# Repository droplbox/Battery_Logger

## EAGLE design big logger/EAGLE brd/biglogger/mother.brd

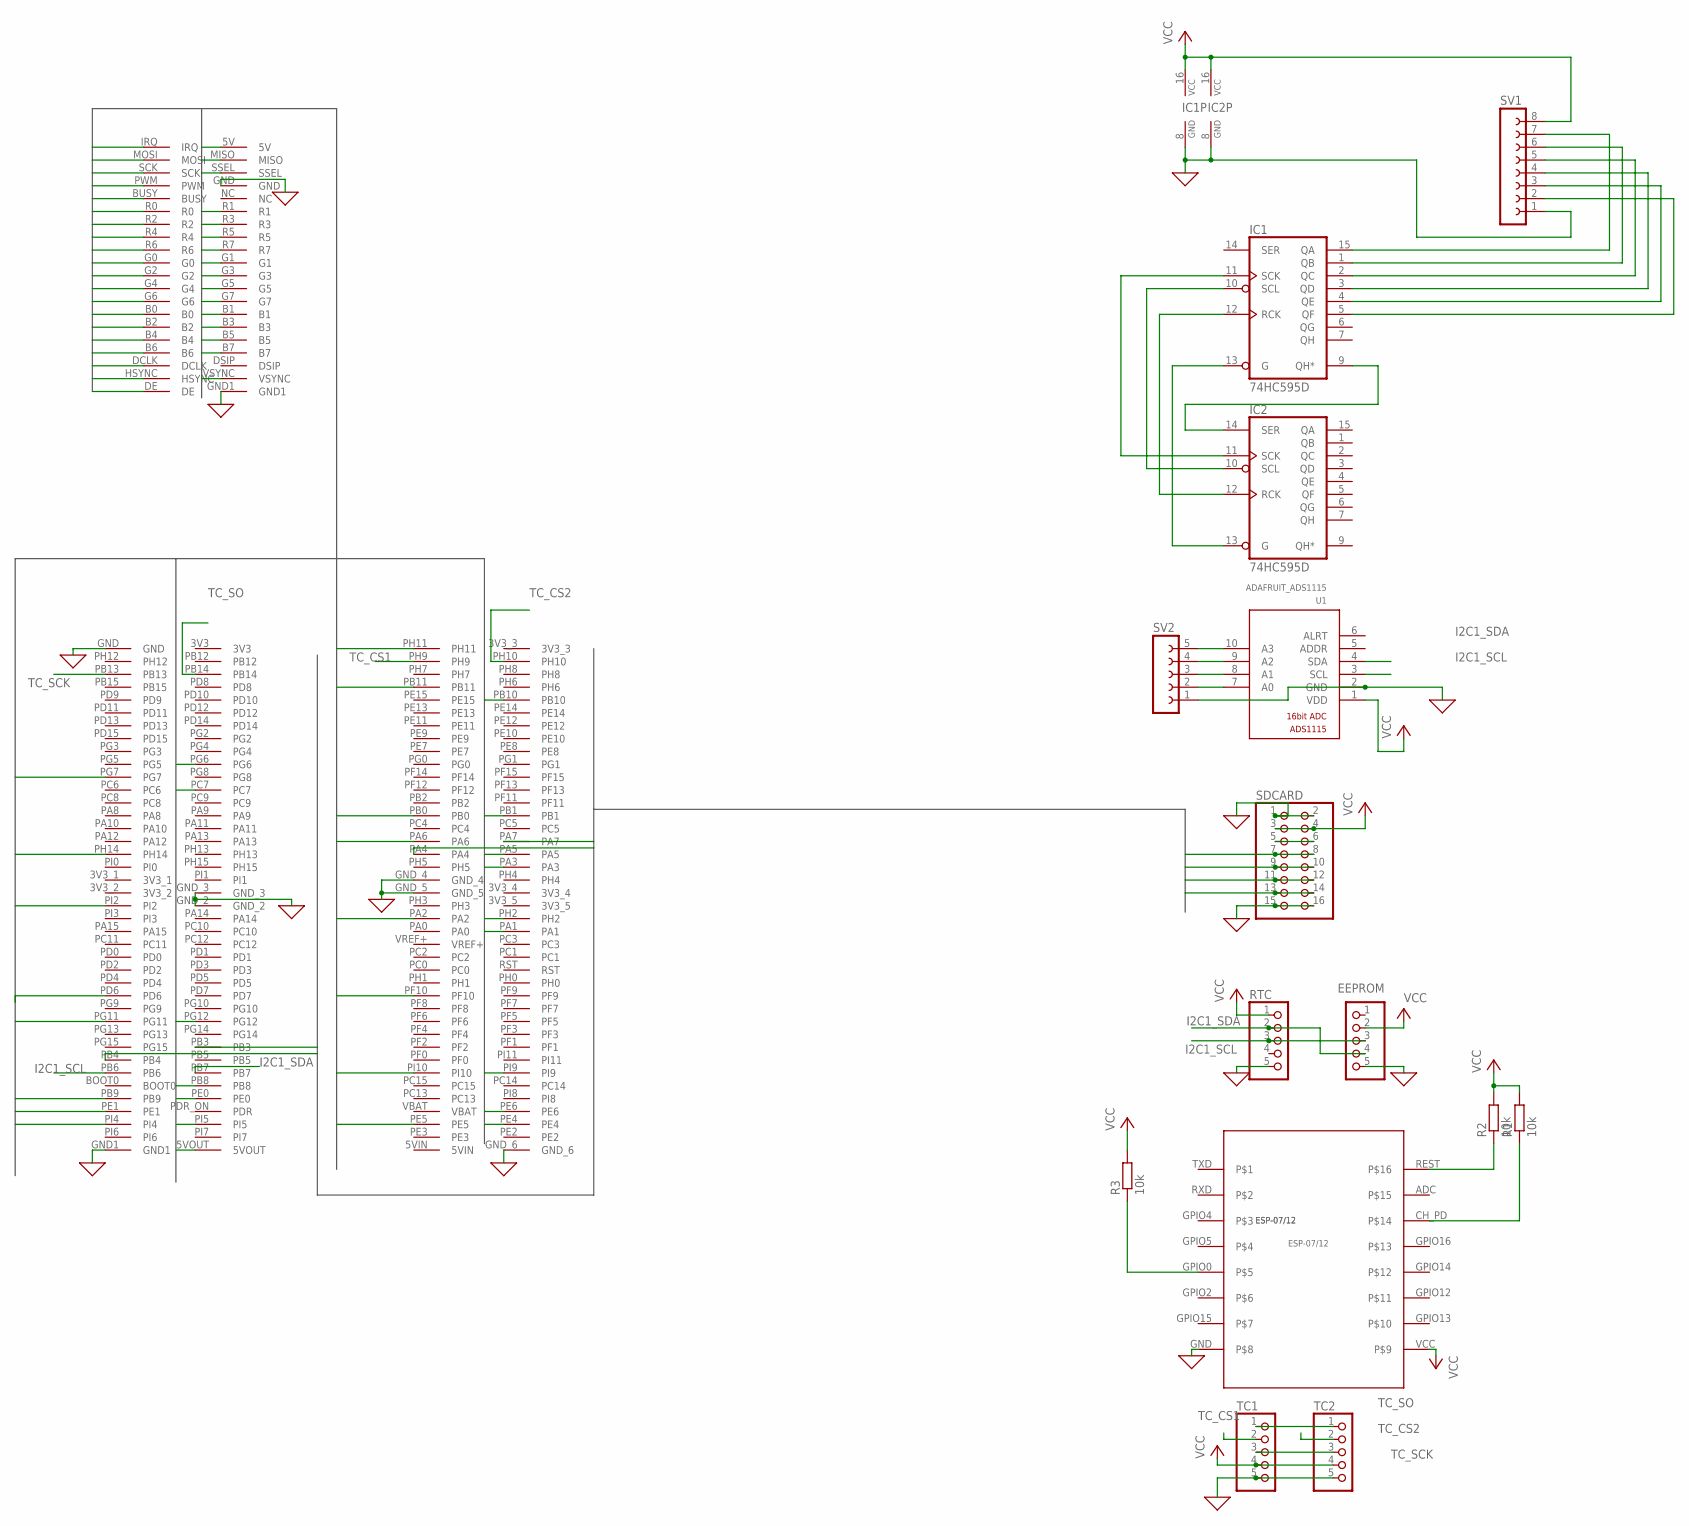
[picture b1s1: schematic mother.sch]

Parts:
EEPROM: PINHD-1X5; 1X05
IC1, IC2: 74HC595D; SO16
R1, R2, R3: 10k; R1206
RTC: PINHD-1X5; 1X05
SDCARD: PINHD-2X8; 2X08
SV1: FE08-1; FE08
SV2: FE05-1
TC1, TC2: PINHD-1X5; 1X05
U1: ADAFRUIT_ADS1115; ADAFRUIT_ADS1115_16BIT_I2C_ADC
U$1: LCDTFT; 4.3LCDTFT
U$2: HEADER2X40_2MM; HEADER
U$3: ESP-07/12

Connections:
0: EEPROM.5, IC1.8 (GND), IC2.8 (GND), RTC.5, SDCARD.1, SDCARD.2, SDCARD.15, SDCARD.16, SV1.1, SV2.1, TC1.5, TC2.5, U1.2 (GND), U$1.GND, U$1.GND1, U$2.GND, U$2.GND1, U$2.GND_2, U$2.GND_3, U$2.GND_4, U$2.GND_5, U$2.GND_6, U$3.GND
5V: U$1.5V, U$2.5VOUT
B0: U$1.B0, U$2.PE4
B1: U$1.B1, U$2.PG12
B2: U$1.B2, U$2.PD6
B3: U$1.B3, U$2.PG11
B4: U$1.B4, U$2.PI4
B5: U$1.B5, U$2.PA3
B6: U$1.B6, U$2.PB8
B7: U$1.B7, U$2.PB9
BUSY: U$1.BUSY, U$2.PE0
CLK: SDCARD.11, SDCARD.12, U$2.PB3
CLK_LTDC: U$1.DCLK, U$2.PG7
CS: SDCARD.7, SDCARD.8, U$2.PA4
DE: U$1.DE, U$2.PF10
G0: U$1.G0, U$2.PE5
G1: U$1.G1, U$2.PE6
G2: U$1.G2, U$2.PA6
G3: U$1.G3, U$2.PH14
G4: U$1.G4, U$2.PB10
G5: U$1.G5, U$2.PB11
G6: U$1.G6, U$2.PC7
G7: U$1.G7, U$2.PI2
HSYNC: U$1.HSYNC, U$2.PI10
I2C1_SCL: EEPROM.3, RTC.3, U1.3 (SCL), U$2.PB6
I2C1_SDA: EEPROM.4, RTC.2, U1.4 (SDA), U$2.PB7
IRQ: U$1.IRQ, U$2.PE1
MISO: SDCARD.13, SDCARD.14, U$2.PB4
MOSI: SDCARD.9, SDCARD.10, U$2.PA7
unnamed: IC1.11 (SCK), IC2.11 (SCK)
unnamed: IC1.10 (SCL), IC2.10 (SCL)
unnamed: IC1.12 (RCK), IC2.12 (RCK)
unnamed: IC1.13 (G), IC2.13 (G)
unnamed: R3.1, U$3.GPIO0
unnamed: IC1.9 (QH*), IC2.14 (SER)
unnamed: SV2.5, U1.10 (A3)
unnamed: SV2.4, U1.9 (A2)
unnamed: IC1.15 (QA), SV1.7
unnamed: IC1.1 (QB), SV1.6
unnamed: IC1.2 (QC), SV1.5
unnamed: IC1.3 (QD), SV1.4
unnamed: IC1.4 (QE), SV1.3
unnamed: IC1.5 (QF), SV1.2
unnamed: SV2.3, U1.8 (A1)
unnamed: SV2.2, U1.7 (A0)
unnamed: R2.1, U$3.REST
unnamed: SDCARD.5, SDCARD.6
unnamed: R1.1, U$3.CH_PD
PWM: U$1.PWM, U$2.PI5
R0: U$1.R0, U$2.PH2
R1: U$1.R1, U$2.PA2
R2: U$1.R2, U$2.PA1
R3: U$1.R3, U$2.PB0
R4: U$1.R4, U$2.PA5
R5: U$1.R5, U$2.PH11
R6: U$1.R6, U$2.PB1
R7: U$1.R7, U$2.PG6
TC_CS1: TC1.2, U$2.PH9
TC_CS2: TC2.2, U$2.PH10
TC_SCK: TC1.3, TC2.3, U$2.PB13
TC_SO: TC1.1, TC2.1, U$2.PB14
TOUCH_MISO: U$1.MISO
TOUCH_MOSI: U$1.MOSI
TOUCH_SCK: U$1.SCK
TOUCH_SS: U$1.SSEL
VCC: EEPROM.2, IC1.16 (VCC), IC2.16 (VCC), R1.2, R2.2, R3.2, RTC.1, SDCARD.3, SDCARD.4, SV1.8, TC1.4, TC2.4, U1.1 (VDD), U$3.VCC
VSYNC: U$1.VSYNC, U$2.PI9

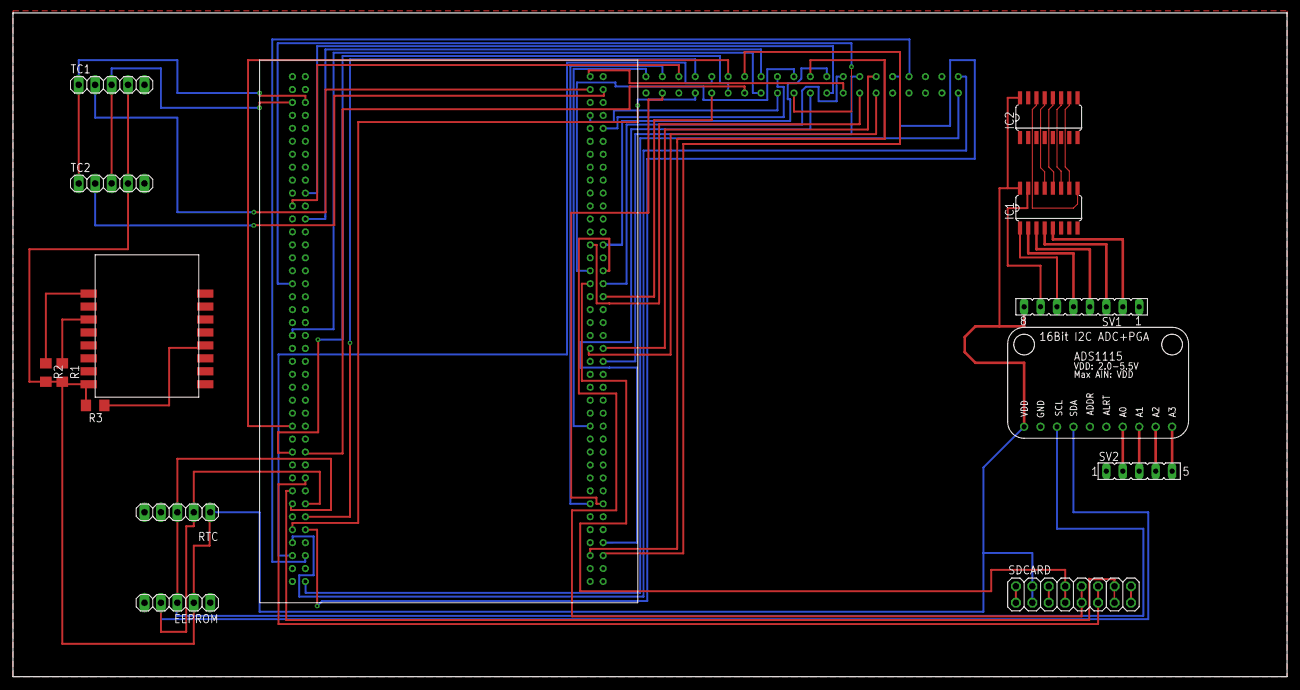
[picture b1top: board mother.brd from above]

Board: 2 copper layers, 196.8 x 102.5 mm, 16 parts (0 on the bottom side), 63 nets.

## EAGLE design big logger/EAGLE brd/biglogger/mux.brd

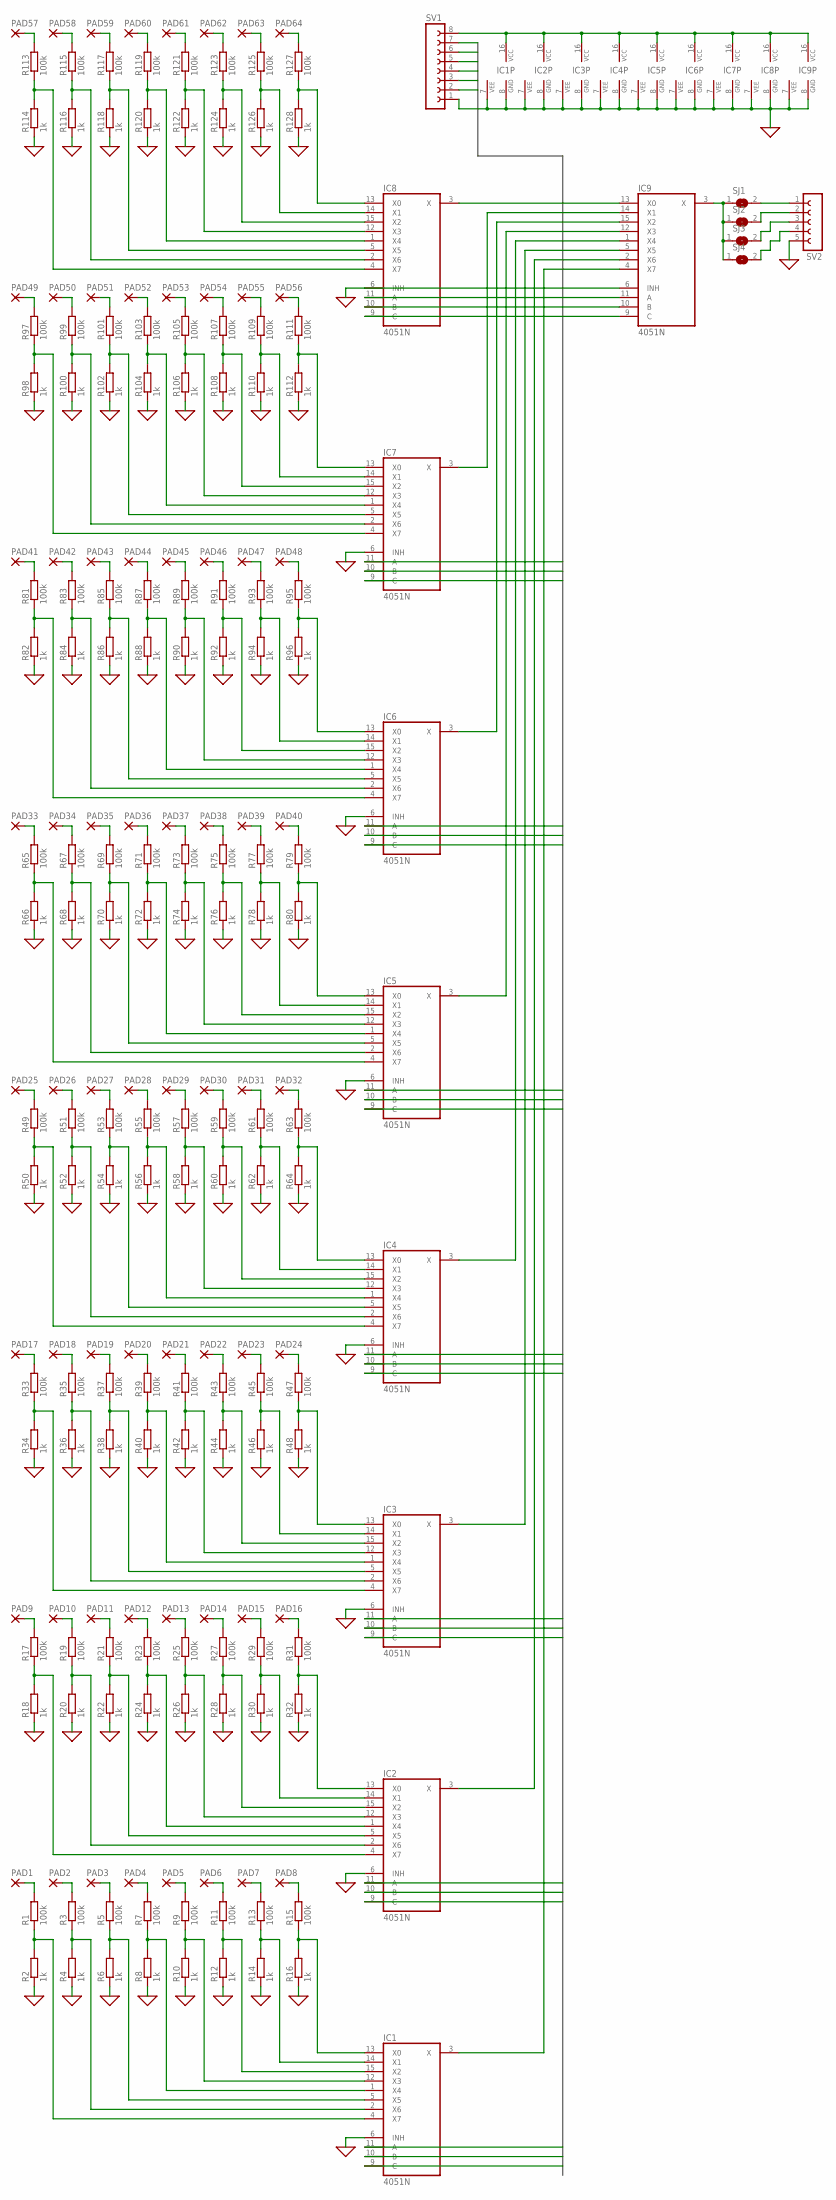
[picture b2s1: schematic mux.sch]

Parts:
IC1, IC2, IC3, IC4, IC5, IC6, IC7, IC8, IC9: 4051N; DIL16
PAD1, PAD2, PAD3, PAD4, PAD5, PAD6, PAD7, PAD8, PAD9, PAD10, PAD11, PAD12, PAD13, PAD14, PAD15, PAD16, PAD17, PAD18, PAD19, PAD20, PAD21, PAD22, PAD23, PAD24, PAD25, PAD26, PAD27, PAD28, PAD29, PAD30, PAD31, PAD32, PAD33, PAD34, PAD35, PAD36, PAD37, PAD38, PAD39, PAD40, PAD41, PAD42, PAD43, PAD44, PAD45, PAD46, PAD47, PAD48, PAD49, PAD50, PAD51, PAD52, PAD53, PAD54, PAD55, PAD56, PAD57, PAD58, PAD59, PAD60, PAD61, PAD62, PAD63, PAD64: 1,6/0,9
R1, R3, R5, R7, R9, R11, R13, R15, R17, R19, R21, R23, R25, R27, R29, R31, R33, R35, R37, R39, R41, R43, R45, R47, R49, R51, R53, R55, R57, R59, R61, R63, R65, R67, R69, R71, R73, R75, R77, R79, R81, R83, R85, R87, R89, R91, R93, R95, R97, R99, R101, R103, R105, R107, R109, R111, R113, R115, R117, R119, R121, R123, R125, R127: 100k; R1206
R2, R4, R6, R8, R10, R12, R14, R16, R18, R20, R22, R24, R26, R28, R30, R32, R34, R36, R38, R40, R42, R44, R46, R48, R50, R52, R54, R56, R58, R60, R62, R64, R66, R68, R70, R72, R74, R76, R78, R80, R82, R84, R86, R88, R90, R92, R94, R96, R98, R100, R102, R104, R106, R108, R110, R112, R114, R116, R118, R120, R122, R124, R126, R128: 1k; R1206
SJ1, SJ2, SJ3, SJ4: SJ
SV1: FE08-1; FE08
SV2: FE05-1

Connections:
0: IC1.6 (INH), IC1.7 (VEE), IC1.8 (GND), IC2.6 (INH), IC2.7 (VEE), IC2.8 (GND), IC3.6 (INH), IC3.7 (VEE), IC3.8 (GND), IC4.6 (INH), IC4.7 (VEE), IC4.8 (GND), IC5.6 (INH), IC5.7 (VEE), IC5.8 (GND), IC6.6 (INH), IC6.7 (VEE), IC6.8 (GND), IC7.6 (INH), IC7.7 (VEE), IC7.8 (GND), IC8.6 (INH), IC8.7 (VEE), IC8.8 (GND), IC9.6 (INH), IC9.7 (VEE), IC9.8 (GND), R2.1, R4.1, R6.1, R8.1, R10.1, R12.1, R14.1, R16.1, R18.1, R20.1, R22.1, R24.1, R26.1, R28.1, R30.1, R32.1, R34.1, R36.1, R38.1, R40.1, R42.1, R44.1, R46.1, R48.1, R50.1, R52.1, R54.1, R56.1, R58.1, R60.1, R62.1, R64.1, R66.1, R68.1, R70.1, R72.1, R74.1, R76.1, R78.1, R80.1, R82.1, R84.1, R86.1, R88.1, R90.1, R92.1, R94.1, R96.1, R98.1, R100.1, R102.1, R104.1, R106.1, R108.1, R110.1, R112.1, R114.1, R116.1, R118.1, R120.1, R122.1, R124.1, R126.1, R128.1, SV1.1, SV2.5
unnamed: IC1.4 (X7), R1.1, R2.2
unnamed: PAD1.1, R1.2
unnamed: IC1.2 (X6), R3.1, R4.2
unnamed: PAD2.1, R3.2
unnamed: IC1.5 (X5), R5.1, R6.2
unnamed: PAD3.1, R5.2
unnamed: IC1.1 (X4), R7.1, R8.2
unnamed: PAD4.1, R7.2
unnamed: IC1.12 (X3), R9.1, R10.2
unnamed: PAD5.1, R9.2
unnamed: IC1.15 (X2), R11.1, R12.2
unnamed: PAD6.1, R11.2
unnamed: IC1.14 (X1), R13.1, R14.2
unnamed: PAD7.1, R13.2
unnamed: IC1.13 (X0), R15.1, R16.2
unnamed: PAD8.1, R15.2
unnamed: IC8.3 (X), IC9.13 (X0)
unnamed: IC2.4 (X7), R17.1, R18.2
unnamed: PAD9.1, R17.2
unnamed: IC2.2 (X6), R19.1, R20.2
unnamed: PAD10.1, R19.2
unnamed: IC2.5 (X5), R21.1, R22.2
unnamed: PAD11.1, R21.2
unnamed: IC2.1 (X4), R23.1, R24.2
unnamed: PAD12.1, R23.2
unnamed: IC2.12 (X3), R25.1, R26.2
unnamed: PAD13.1, R25.2
unnamed: IC2.15 (X2), R27.1, R28.2
unnamed: PAD14.1, R27.2
unnamed: IC2.14 (X1), R29.1, R30.2
unnamed: PAD15.1, R29.2
unnamed: IC2.13 (X0), R31.1, R32.2
unnamed: PAD16.1, R31.2
unnamed: IC3.4 (X7), R33.1, R34.2
unnamed: PAD17.1, R33.2
unnamed: IC3.2 (X6), R35.1, R36.2
unnamed: PAD18.1, R35.2
unnamed: IC3.5 (X5), R37.1, R38.2
unnamed: PAD19.1, R37.2
unnamed: IC3.1 (X4), R39.1, R40.2
unnamed: PAD20.1, R39.2
unnamed: IC3.12 (X3), R41.1, R42.2
unnamed: PAD21.1, R41.2
unnamed: IC3.15 (X2), R43.1, R44.2
unnamed: PAD22.1, R43.2
unnamed: IC3.14 (X1), R45.1, R46.2
unnamed: PAD23.1, R45.2
unnamed: IC3.13 (X0), R47.1, R48.2
unnamed: PAD24.1, R47.2
unnamed: IC4.4 (X7), R49.1, R50.2
unnamed: PAD25.1, R49.2
unnamed: IC4.2 (X6), R51.1, R52.2
unnamed: PAD26.1, R51.2
unnamed: IC4.5 (X5), R53.1, R54.2
unnamed: PAD27.1, R53.2
unnamed: IC4.1 (X4), R55.1, R56.2
unnamed: PAD28.1, R55.2
unnamed: IC4.12 (X3), R57.1, R58.2
unnamed: PAD29.1, R57.2
unnamed: IC4.15 (X2), R59.1, R60.2
unnamed: PAD30.1, R59.2
unnamed: IC4.14 (X1), R61.1, R62.2
unnamed: PAD31.1, R61.2
unnamed: IC4.13 (X0), R63.1, R64.2
unnamed: PAD32.1, R63.2
unnamed: IC5.4 (X7), R65.1, R66.2
unnamed: PAD33.1, R65.2
unnamed: IC5.2 (X6), R67.1, R68.2
unnamed: PAD34.1, R67.2
unnamed: IC5.5 (X5), R69.1, R70.2
unnamed: PAD35.1, R69.2
unnamed: IC5.1 (X4), R71.1, R72.2
unnamed: PAD36.1, R71.2
unnamed: IC5.12 (X3), R73.1, R74.2
unnamed: PAD37.1, R73.2
unnamed: IC5.15 (X2), R75.1, R76.2
unnamed: PAD38.1, R75.2
unnamed: IC5.14 (X1), R77.1, R78.2
unnamed: PAD39.1, R77.2
unnamed: IC5.13 (X0), R79.1, R80.2
unnamed: PAD40.1, R79.2
unnamed: IC6.4 (X7), R81.1, R82.2
unnamed: PAD41.1, R81.2
unnamed: IC6.2 (X6), R83.1, R84.2
unnamed: PAD42.1, R83.2
unnamed: IC6.5 (X5), R85.1, R86.2
unnamed: PAD43.1, R85.2
unnamed: IC6.1 (X4), R87.1, R88.2
unnamed: PAD44.1, R87.2
unnamed: IC6.12 (X3), R89.1, R90.2
unnamed: PAD45.1, R89.2
unnamed: IC6.15 (X2), R91.1, R92.2
unnamed: PAD46.1, R91.2
unnamed: IC6.14 (X1), R93.1, R94.2
unnamed: PAD47.1, R93.2
unnamed: IC6.13 (X0), R95.1, R96.2
unnamed: PAD48.1, R95.2
unnamed: IC7.4 (X7), R97.1, R98.2
unnamed: PAD49.1, R97.2
unnamed: IC7.2 (X6), R99.1, R100.2
unnamed: PAD50.1, R99.2
unnamed: IC7.5 (X5), R101.1, R102.2
unnamed: PAD51.1, R101.2
unnamed: IC7.1 (X4), R103.1, R104.2
unnamed: PAD52.1, R103.2
unnamed: IC7.12 (X3), R105.1, R106.2
unnamed: PAD53.1, R105.2
unnamed: IC7.15 (X2), R107.1, R108.2
unnamed: PAD54.1, R107.2
unnamed: IC7.14 (X1), R109.1, R110.2
unnamed: PAD55.1, R109.2
unnamed: IC7.13 (X0), R111.1, R112.2
unnamed: PAD56.1, R111.2
unnamed: IC8.4 (X7), R113.1, R114.2
unnamed: PAD57.1, R113.2
unnamed: IC8.2 (X6), R115.1, R116.2
unnamed: PAD58.1, R115.2
unnamed: IC8.5 (X5), R117.1, R118.2
unnamed: PAD59.1, R117.2
unnamed: IC8.1 (X4), R119.1, R120.2
unnamed: PAD60.1, R119.2
unnamed: IC8.12 (X3), R121.1, R122.2
unnamed: PAD61.1, R121.2
unnamed: IC8.15 (X2), R123.1, R124.2
unnamed: PAD62.1, R123.2
unnamed: IC8.14 (X1), R125.1, R126.2
unnamed: PAD63.1, R125.2
unnamed: IC8.13 (X0), R127.1, R128.2
unnamed: PAD64.1, R127.2
unnamed: IC7.3 (X), IC9.14 (X1)
unnamed: IC6.3 (X), IC9.15 (X2)
unnamed: IC5.3 (X), IC9.12 (X3)
unnamed: IC4.3 (X), IC9.1 (X4)
unnamed: IC3.3 (X), IC9.5 (X5)
unnamed: IC2.3 (X), IC9.2 (X6)
unnamed: IC1.3 (X), IC9.4 (X7)
unnamed: IC9.3 (X), SJ1.1, SJ2.1, SJ3.1, SJ4.1
unnamed: SJ1.2, SV2.1
unnamed: SJ2.2, SV2.2
unnamed: SJ3.2, SV2.3
unnamed: SJ4.2, SV2.4
REG1: IC1.11 (A), IC2.11 (A), IC3.11 (A), IC4.11 (A), IC5.11 (A), IC6.11 (A), IC7.11 (A), IC8.11 (A), SV1.7
REG2: IC1.10 (B), IC2.10 (B), IC3.10 (B), IC4.10 (B), IC5.10 (B), IC6.10 (B), IC7.10 (B), IC8.10 (B), SV1.6
REG3: IC1.9 (C), IC2.9 (C), IC3.9 (C), IC4.9 (C), IC5.9 (C), IC6.9 (C), IC7.9 (C), IC8.9 (C), SV1.5
REG4: IC9.11 (A), SV1.4
REG5: IC9.10 (B), SV1.3
REG6: IC9.9 (C), SV1.2
VCC: IC1.16 (VCC), IC2.16 (VCC), IC3.16 (VCC), IC4.16 (VCC), IC5.16 (VCC), IC6.16 (VCC), IC7.16 (VCC), IC8.16 (VCC), IC9.16 (VCC), SV1.8

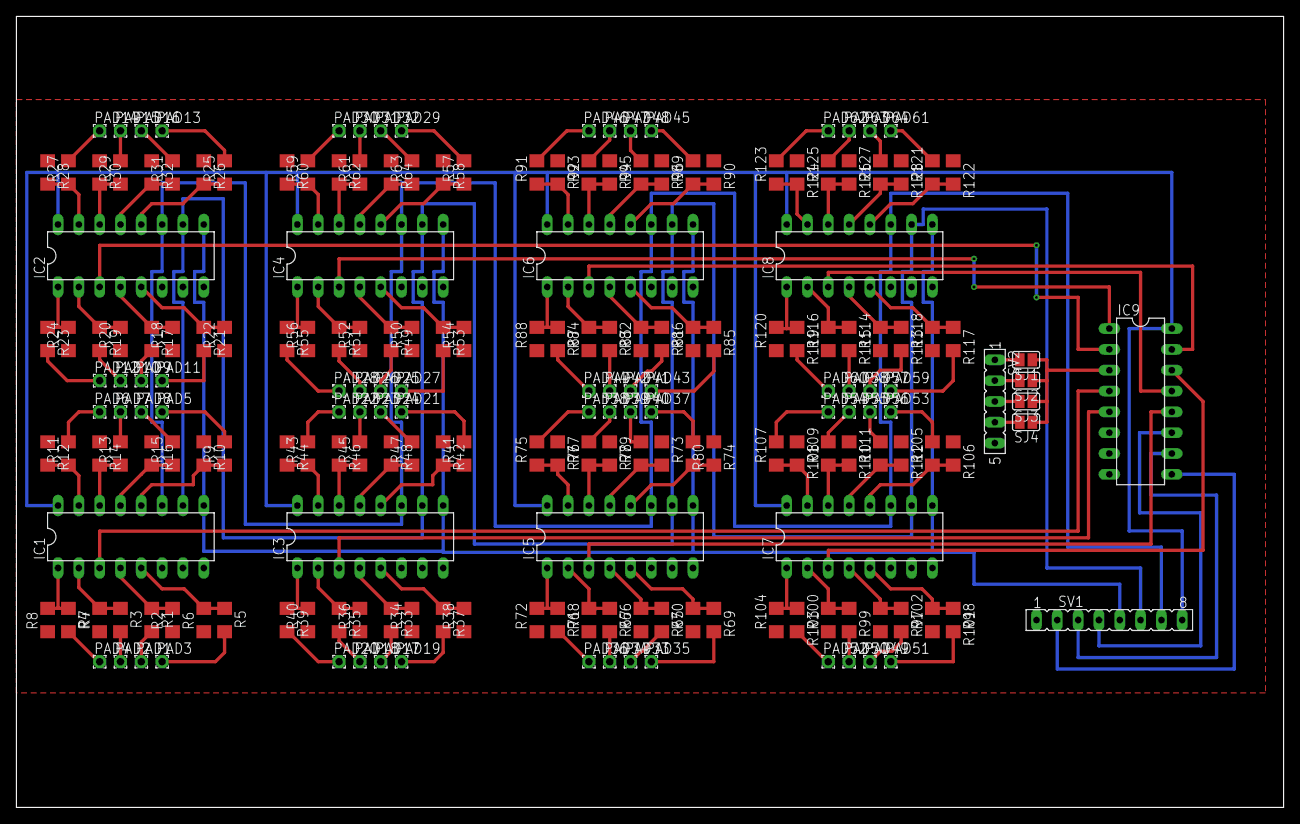
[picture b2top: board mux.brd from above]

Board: 2 copper layers, 154.6 x 96.5 mm, 207 parts (0 on the bottom side), 149 nets.

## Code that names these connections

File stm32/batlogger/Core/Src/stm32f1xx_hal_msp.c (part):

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
    __HAL_RCC_GPIOB_CLK_ENABLE();
    /**I2C1 GPIO Configuration
    PB6     ------> I2C1_SCL
    PB7     ------> I2C1_SDA
    */
    GPIO_InitStruct.Pin = GPIO_PIN_6|GPIO_PIN_7;
    GPIO_InitStruct.Mode = GPIO_MODE_AF_OD;
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    __HAL_RCC_I2C1_CLK_DISABLE();

    /**I2C1 GPIO Configuration
    PB6     ------> I2C1_SCL
    PB7     ------> I2C1_SDA
    */
    HAL_GPIO_DeInit(GPIOB, GPIO_PIN_6);

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
    __HAL_RCC_GPIOA_CLK_ENABLE();
    /**SPI1 GPIO Configuration
    PA5     ------> SPI1_SCK
    PA6     ------> SPI1_MISO
    */
    GPIO_InitStruct.Pin = GPIO_PIN_5;
    GPIO_InitStruct.Mode = GPIO_MODE_AF_PP;
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
    __HAL_RCC_GPIOB_CLK_ENABLE();
    /**SPI2 GPIO Configuration
    PB13     ------> SPI2_SCK
    PB14     ------> SPI2_MISO
    PB15     ------> SPI2_MOSI
    */
    GPIO_InitStruct.Pin = GPIO_PIN_13|GPIO_PIN_15;
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    __HAL_RCC_SPI1_CLK_DISABLE();

    /**SPI1 GPIO Configuration
    PA5     ------> SPI1_SCK
    PA6     ------> SPI1_MISO
    */
    HAL_GPIO_DeInit(GPIOA, GPIO_PIN_5|GPIO_PIN_6);

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    __HAL_RCC_SPI2_CLK_DISABLE();

    /**SPI2 GPIO Configuration
    PB13     ------> SPI2_SCK
    PB14     ------> SPI2_MISO
    PB15     ------> SPI2_MOSI
    */
    HAL_GPIO_DeInit(GPIOB, GPIO_PIN_13|GPIO_PIN_14|GPIO_PIN_15);
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
    __HAL_RCC_GPIOB_CLK_ENABLE();
    /**TIM3 GPIO Configuration
    PB4     ------> TIM3_CH1
    */
    GPIO_InitStruct.Pin = LED_Pin;
    GPIO_InitStruct.Mode = GPIO_MODE_AF_OD;
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
    __HAL_RCC_GPIOA_CLK_ENABLE();
    /**USART2 GPIO Configuration
    PA2     ------> USART2_TX
    PA3     ------> USART2_RX
    */
    GPIO_InitStruct.Pin = GPIO_PIN_2;
    GPIO_InitStruct.Mode = GPIO_MODE_AF_PP;
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    __HAL_RCC_USART2_CLK_DISABLE();

    /**USART2 GPIO Configuration
    PA2     ------> USART2_TX
    PA3     ------> USART2_RX
    */
    HAL_GPIO_DeInit(GPIOA, GPIO_PIN_2|GPIO_PIN_3);

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
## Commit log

2022-12-19 init
2023-01-16 bg upd

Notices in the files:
stm32/batlogger/Core/Src/stm32f1xx_hal_msp.c:
Copyright (c) 2022 STMicroelectronics.
All rights reserved.
This software is licensed under terms that can be found in the LICENSE file
